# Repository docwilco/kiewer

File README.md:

# kiewer

A site for uploading and sharing KiCad designs, rendered in the browser. The design is in `docs/v1-scope.md` and `docs/adr/`; the vocabulary in `GLOSSARY.md`.

## Development

One-time, after cloning: `git config core.hooksPath .githooks`, then for
the viewer's browser build `rustup target add wasm32-unknown-unknown` and
`cargo install wasm-bindgen-cli --version "$(scripts/wasm-bindgen-version.sh)" --locked`,
and for the sqlx stage
`cargo install sqlx-cli --version "$(scripts/sqlx-version.sh)" --locked --no-default-features --features postgres,rustls`
(each the version Cargo.lock names; CI installs the same way). The hook runs
`scripts/checks.sh` (the stages are listed in its usage line) before every
commit against a snapshot of the index, so unstaged edits never reach the
checks and the working tree stays usable while they run; it needs `rsync`,
`jq` and `cargo-sweep`. CI runs the same script. Run a single stage with
`scripts/checks.sh clippy`. The same setting enables a post-merge hook:
after a merge or pull, fast-forwards included, it removes what the
checkout's target has not used in three days (`.githooks/sweep.sh`, which
the pre-commit hook runs too), and prints a line when it skips.

Running the server: `docker compose up -d` starts Postgres (`compose.yaml`),
`cp .env.example .env` and export it (`set -a; . ./.env; set +a`),
`scripts/build-viewer.sh` once (and again after a change to `kiewer_viewer`
or `kicad_core`: it writes the browser viewer to `kiewer_viewer/dist`, which
`cargo run` embeds; without it the server runs and the viewer page says the
viewer is not built in), then `cargo run`. The first line on stdout is the
build line; the page is at http://localhost:8090/, the viewer with the
hand-off board at http://localhost:8090/viewer, its schematic at
http://localhost:8090/schematic, the upload form at
http://localhost:8090/upload once signed in, and `/health` says `ok` once
the database answers.
`kiewer_lib::config` is the list of variables the server reads and their
defaults; the blob store writes under `blobs/` (git-ignored) unless
`BLOB_BUCKET` names a GCS bucket, which makes it the GCS store (with
`KIEWER_GCS_EMULATOR` beside it, on the emulator below). `FASTLY_SERVICE_ID`
and `FASTLY_API_TOKEN` stay unset here: nothing is in front of the server,
so a write purges nothing. `SURROGATE_KEY_PREFIX` goes in front of every
cache key the server names and purges; `infra/` sets `staging-` on
kiewer-staging, which shares production's Fastly service, and a dev box
leaves it unset. The log is text
on a terminal and JSON lines anywhere else (Cloud Run reads those into
`jsonPayload`; the renderer beacon's metric in `infra/logging.tf` counts
them); `LOG_FORMAT=json` or `text` overrides. Ctrl-c or SIGTERM stops it
after the requests in flight.

The tests that need Postgres (every user of `kiewer_test_support::db`)
run when `DATABASE_URL` is exported; CI sets it against a service
container that matches `compose.yaml`. Without it such a test returns
early and counts as passed, so `scripts/checks.sh test` fails without
it, unless `KIEWER_SKIP_DB_TESTS=1` is set: then they skip, and a loud
line names them before the stages and again after the last. CI refuses
the opt-out. The hook reads the variable from the shell that runs
`git commit`, never from `.env`: each worktree needs a database of its
own, since on a shared one sqlx refuses a worktree that lacks a
migration another applied (`VersionMissing`). Some test modules create
and use a database of their own beside it, the URL's name plus a suffix
(`kiewer_test_support::db::pool_of_its_own`: `_collector`, `_plans`), so
the role needs CREATEDB (compose's and CI's `kiewer` is the image's
superuser). The schema is `migrations/` (its README has the
naming rule).

Every statement in `kiewer_lib` is a `sqlx::query!`, `query_as!` or
`query_scalar!` macro, checked at compile time against the offline data
committed in `.sqlx/`; statement text several statements share is spliced
in by `kiewer_lib/src/sql.rs`. `scripts/checks.sh` and
`scripts/release-build.sh` export `SQLX_OFFLINE=true`, so a build reads
that data and never a database; `.env.example` sets it too, since the
macros read a `.env` here or in any directory above. After a change to a
statement or a migration, `scripts/sqlx-prepare.sh` rewrites `.sqlx/`
against a scratch database beside `DATABASE_URL`'s (its name plus
`_sqlx`, migrated from `migrations/`), and `git add -A .sqlx` stages the
new and the deleted files with the change. The sqlx stage runs it with
`--check` and fails while the data is stale. While a statement is in
flux, build with `SQLX_OFFLINE=false` and `DATABASE_URL` on that scratch
database, which the last prepare left migrated.

Sign-in needs an OAuth app of your own at each provider you want, one per
environment (docs/v1-scope.md, Q57). The callback URL to register is
`PUBLIC_URL` (default `http://localhost:8090`, localhost on `PORT`) plus
`/auth/<provider>/callback`; the client id and secret go in `.env` as
`OAUTH_<PROVIDER>_CLIENT_ID` and `OAUTH_<PROVIDER>_CLIENT_SECRET`, the
names `infra/` hands Cloud Run too. A provider with neither variable is
left off the front page and its `/auth/<provider>` answers 404; one
variable without the other fails startup naming the missing one.

- GitHub: https://github.com/settings/developers, New OAuth App, any name,
  homepage `http://localhost:8090`, callback
  `http://localhost:8090/auth/github/callback`; generate a client secret.
  Variables `OAUTH_GITHUB_*`.
- Discord: https://discord.com/developers/applications, New Application,
  OAuth2, add the redirect `http://localhost:8090/auth/discord/callback`;
  the client id and secret are on that page. The server asks the
  `identify` scope only. Variables `OAUTH_DISCORD_*`.
- Google: https://console.cloud.google.com/apis/credentials, Create
  credentials, OAuth client ID, Web application, authorised redirect URI
  `http://localhost:8090/auth/google/callback`; the consent screen needs
  the `profile` scope only and, while it is in testing, your account as
  a test user. Variables `OAUTH_GOOGLE_*`.

Cookies are `Secure` under an `https` `PUBLIC_URL`, so a dev box over
`http` works in every browser. The sign-in tests use a fake of each
provider on loopback and need no app. Production and staging get their
registrations through Secret Manager, not `.env`.

The GCS store test (`kiewer_lib/tests/it/gcs_blob_store.rs`) runs when
`KIEWER_GCS_EMULATOR` names a
[fake-gcs-server](https://github.com/fsouza/fake-gcs-server), under the
same rule as Postgres: without it `scripts/checks.sh test` fails, unless
`KIEWER_SKIP_GCS_TESTS=1` is set, which CI refuses. On a dev box: the
release binary for your platform (v1.56.1, the version CI pins), then
`fake-gcs-server -scheme http -host 127.0.0.1 -port 8092 -backend memory -public-host 127.0.0.1`
and `export KIEWER_GCS_EMULATOR=http://127.0.0.1:8092`.

The golden-image test (`kiewer_viewer/tests/golden.rs`) renders the
hand-off board headless through wgpu on Vulkan and compares each view
with `viewer-drop/exports/png`; its tolerance is in its module doc. It
needs a Vulkan driver: on a box without a GPU that is Mesa's lavapipe,
`apt install mesa-vulkan-drivers`, the package CI and the Dockerfile
install. Without one it skips with a line saying so; on CI it fails
instead. `cargo run --bin kiewer_render_dev -- viewer-drop/board/midi8knob.kicad_pcb <dir>`
writes the same PNGs for a look.

The browser stage (`scripts/checks.sh browser`, in `all`) loads the board
page in Chrome for Testing's `chrome-headless-shell`, which draws WebGL2 on
SwiftShader with no GPU (`kiewer_lib/tests/it/browser.rs`). On a dev box:
`sudo apt install $(scripts/browser.sh packages)` for the libraries it
links against (Ubuntu 24.04 names), then `scripts/browser.sh install`,
which downloads the version the script pins, checks its SHA-256 and
unpacks it under `~/.cache/kiewer` (it needs `curl` and `unzip`); CI
installs the same way. Without it the stage skips with a line saying so;
on CI it fails instead. The Dockerfile installs neither, though programs
the tests run otherwise go into all three places: the image is
runtime-only and runs no tests.

Clippy is pedantic with no blanket allows: every finding is fixed or carries a
site-level `#[expect(..., reason = "...")]` naming the invariant that makes it safe.

### Exit codes

The executable's non-zero exits, each a kind of `kiewer_lib::error::Error`
(`Exit` there renders this table; a test keeps the two equal). 0 is success;
1, 2, 101 and 126 up are never assigned.

| Code | Kind | Meaning |
|---|---|---|
| 3 | Io | I/O, including the blob store's files |
| 4 | Blob | a blob that is corrupt or a hash that does not parse |
| 5 | Config | the environment is missing or malformed |
| 6 | Db | Postgres, including migrations |
| 7 | Template | a page did not render |
| 8 | Failed | a failure with no better kind |
| 9 | Upstream | a sign-in provider or another service over HTTP |

`kiewer_render_dev`'s, each a kind of `kiewer_viewer::error::Error` (`Exit`
there, the same way); 2 is a usage error.

| Code | Kind | Meaning |
|---|---|---|
| 3 | Io | reading the board or writing a PNG |
| 4 | Board | the board does not parse or has nothing to draw |
| 5 | Gpu | no Vulkan adapter, no device, or a frame that would not read back |
| 6 | Png | a PNG that would not encode or decode |

## Infrastructure

GCP and Fastly are Terraform in `infra/`, applied by hand from a workstation;
CI only deploys Cloud Run revisions with the identity it defines there.
`infra/README.md` is the procedure: bootstrapping the state bucket, the apply,
setting the three repository variables from the outputs, and what a plan after
a CI deploy should show.

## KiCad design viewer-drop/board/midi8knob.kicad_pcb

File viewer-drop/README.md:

# midi8knob board viewer: hand-off

Goal: a website, in the spirit of KiCanvas, that shows this KiCad board as
the eight views below plus the schematic, with pan and zoom, layer toggles,
and labels that become readable as you zoom in. Everything in this folder is
the current static pipeline that produces those views; the site replaces the
static output, not the conventions.

Owner: DocWilco. Board: 8 rotary encoders with WS2812B LEDs, STM32G431KBT6,
USB-C, 4 copper layers.

## What is here

| Path | What |
|---|---|
| `board/midi8knob.kicad_pcb` | The board, KiCad 10 format, with the "Rescue" items already stripped (see gotchas). |
| `board/midi8knob.kicad_sch`, `board/midi8knob.kicad_pro` | Schematic and project. |
| `tools/` | The pipeline. `make-svgs.sh` runs everything; read it first. |
| `exports/midi8knob-<layer>.svg` | One kicad-cli export per layer, board-area page, no drawing sheet. |
| `exports/labels-<layer>.svg`, `labels-<layer>-mirror.svg` | Visible pad, via and track labels per copper layer, from `tools/net_labels.py`. |
| `exports/holes.svg` | Drill holes with copper rims on plated ones, from `tools/holes.py`. |
| `exports/views/NN-*.svg`, `exports/midi8knob-layers.svg` | The eight composed views and the tiled overview, from `tools/compose_svg.py`. |
| `exports/png/` | PNG of every view, the overview, and the schematic. The reference rendering: match these. |
| `exports/midi8knob-schematic.svg` | `kicad-cli sch export svg`, one sheet, A4 landscape. |

## The eight views

Layers stack bottom to top. "board" is the brown FR4 fill from the Edge.Cuts
outline; "bare" is outline only. "labels" are the per-layer label files,
drawn last. "holes" is `holes.svg`.

| # | Header | Stack |
|---|---|---|
| 1 | F.Cu + F.Paste | bare, F.Cu `#C83434`, F.Paste silver, labels F |
| 2 | In1.Cu | bare, In1.Cu `#7FC87F`, labels In1 |
| 3 | In2.Cu | bare, In2.Cu `#CE7D2C`, labels In2 |
| 4 | B.Cu | bare, B.Cu `#4D7FC4`, labels B |
| 5 | F.Cu + F.Paste + F.Mask + F.SilkS | board, F.Cu copper, mask overlay with F.Mask openings, F.Paste, F.SilkS, holes, labels F |
| 6 | B.Cu + B.Paste + B.Mask + B.SilkS, mirrored | as 5 with B layers, whole panel flipped left-right, labels from the `-mirror` file drawn unflipped |
| 7 | F.Cu + B.Cu + F.SilkS + B.SilkS + F.CrtYd + B.CrtYd | bare, B.Cu `#4D7FC4`, F.Cu `#C83434` at opacity 0.8, B.SilkS, F.SilkS, B.CrtYd `#26E9FF`, F.CrtYd `#FF26E2`, holes, labels B then F |
| 8 | B.Cu + F.Cu + ... | as 7 with F.Cu underneath and B.Cu on top at 0.8, labels F then B |

Colours (`tools/compose_svg.py`, duplicated in `tools/holes.py`): page
`#2b2b2b`, board `#7a5a32`, copper `#f0c030`, paste `#c9c9c9`, mask
`#1f8a3f` at opacity 0.7, outline `#D0D2CD`. Views 1 to 4 and 7, 8 use the
KiCad default theme colours instead of copper yellow.

## How a view is composed

- **Coordinates.** Every export shares one viewBox, `0 0 111.9886 57.9882`
  mm, origin at the Edge.Cuts bounding box (kicad-cli `--page-size-mode 2`).
  Board coordinates map to it by subtracting the Edge.Cuts minimum, which
  `tools/kicad_board.py` computes. Labels and holes are generated straight
  from the board file in that frame.
- **Board fill.** The Edge.Cuts export is stroked segments and arcs;
  `outline_path()` chains them into one closed path.
- **Mask overlay.** The mask layer in KiCad is the openings. The overlay is
  the board path in mask colour with an SVG luminance `<mask>` that is white
  everywhere and black where the F.Mask/B.Mask export has shapes.
- **Holes.** kicad-cli draws drill marks white on copper layers and black on
  every other layer; the composer recolours both to the page background.
  `holes.svg` redraws them with a copper rim for plated holes, from pad
  type (`thru_hole` plated, `np_thru_hole` bare) and via drill.
- **Labels.** Pad number and net inside the pad, net on vias and along
  track segments. Font size fits the item (monospace, 0.6 em per glyph),
  labels under 0.08 mm are dropped. Angle follows the pad or track long
  axis, normalised to (-90, 90]; round and square pads stay upright.
- **Mirror.** `<g transform="translate(w 0) scale(-1 1)">` around the
  layers; label files for mirrored views have x flipped and angles negated
  so the text reads normally.
- **Zoom.** The composed SVGs declare width and height 10x the viewBox
  because browsers cap zoom relative to the natural size. A site with its
  own pan/zoom drops that.

## kicad-cli SVG conventions worth knowing

- Shapes carry colour in `style="fill:#RRGGBB; ..."` strings, theme colours
  per layer. Recolouring is a string replace on those.
- Oval pads and oval mask openings are round-capped stroked `<path>` lines,
  not filled shapes. Anything that treats "fill" as the only colour misses
  them.
- Text on the silkscreen is already paths; the exports need no font. The
  label files use `font-family="Consolas, monospace"` as live `<text>`.
- `--subtract-soldermask` was on for the silkscreen export.

## Gotchas

- **Rescue layer.** The JLCPCB-converted footprints (J1 USB-C, SW5, SW10)
  carry body art on an undefined "Rescue" layer. The KiCad GUI tolerates it;
  kicad-cli refuses the board. `tools/strip_rescue.py` writes a cleaned copy,
  and `board/midi8knob.kicad_pcb` here is that copy.
- **Fonts.** Silkscreen uses Consolas with knockout. Regenerating the
  exports with kicad-cli needs the font installed (`~/.fonts/consola.ttf`,
  `fc-cache -f`); otherwise it substitutes DejaVu Sans Mono and the labels
  shift. Not in this folder; proprietary.
- **File names.** `kicad-cli sch export svg` names its output after the
  project, `midi8knob.svg`, which collides with the `midi8knob.svg/` output
  directory in the repo. The pipeline exports to a temp dir and moves it.
- **Line endings.** Board and schematic files are CRLF. Nets are written as
  `(net "name")` without numbers in this format version.
- **Dependencies** to rerun the pipeline: kicad-cli 10.0.8 (Ubuntu PPA
  `ppa:kicad/kicad-10.0-releases`), `rsvg-convert` from `librsvg2-bin`,
  Python 3, the font above.

## Open

- Site stack is undecided. KiCanvas itself parses `.kicad_pcb` and renders
  in WebGL; this pipeline instead pre-renders with kicad-cli. Either route
  must reproduce the eight stacks and the label and hole rules above.
- Whether the site reads the board file at runtime or ships the exports.
- Hover or click on a net to highlight it is wanted but not built; the
  label files and `tools/kicad_board.py` give net names per item.

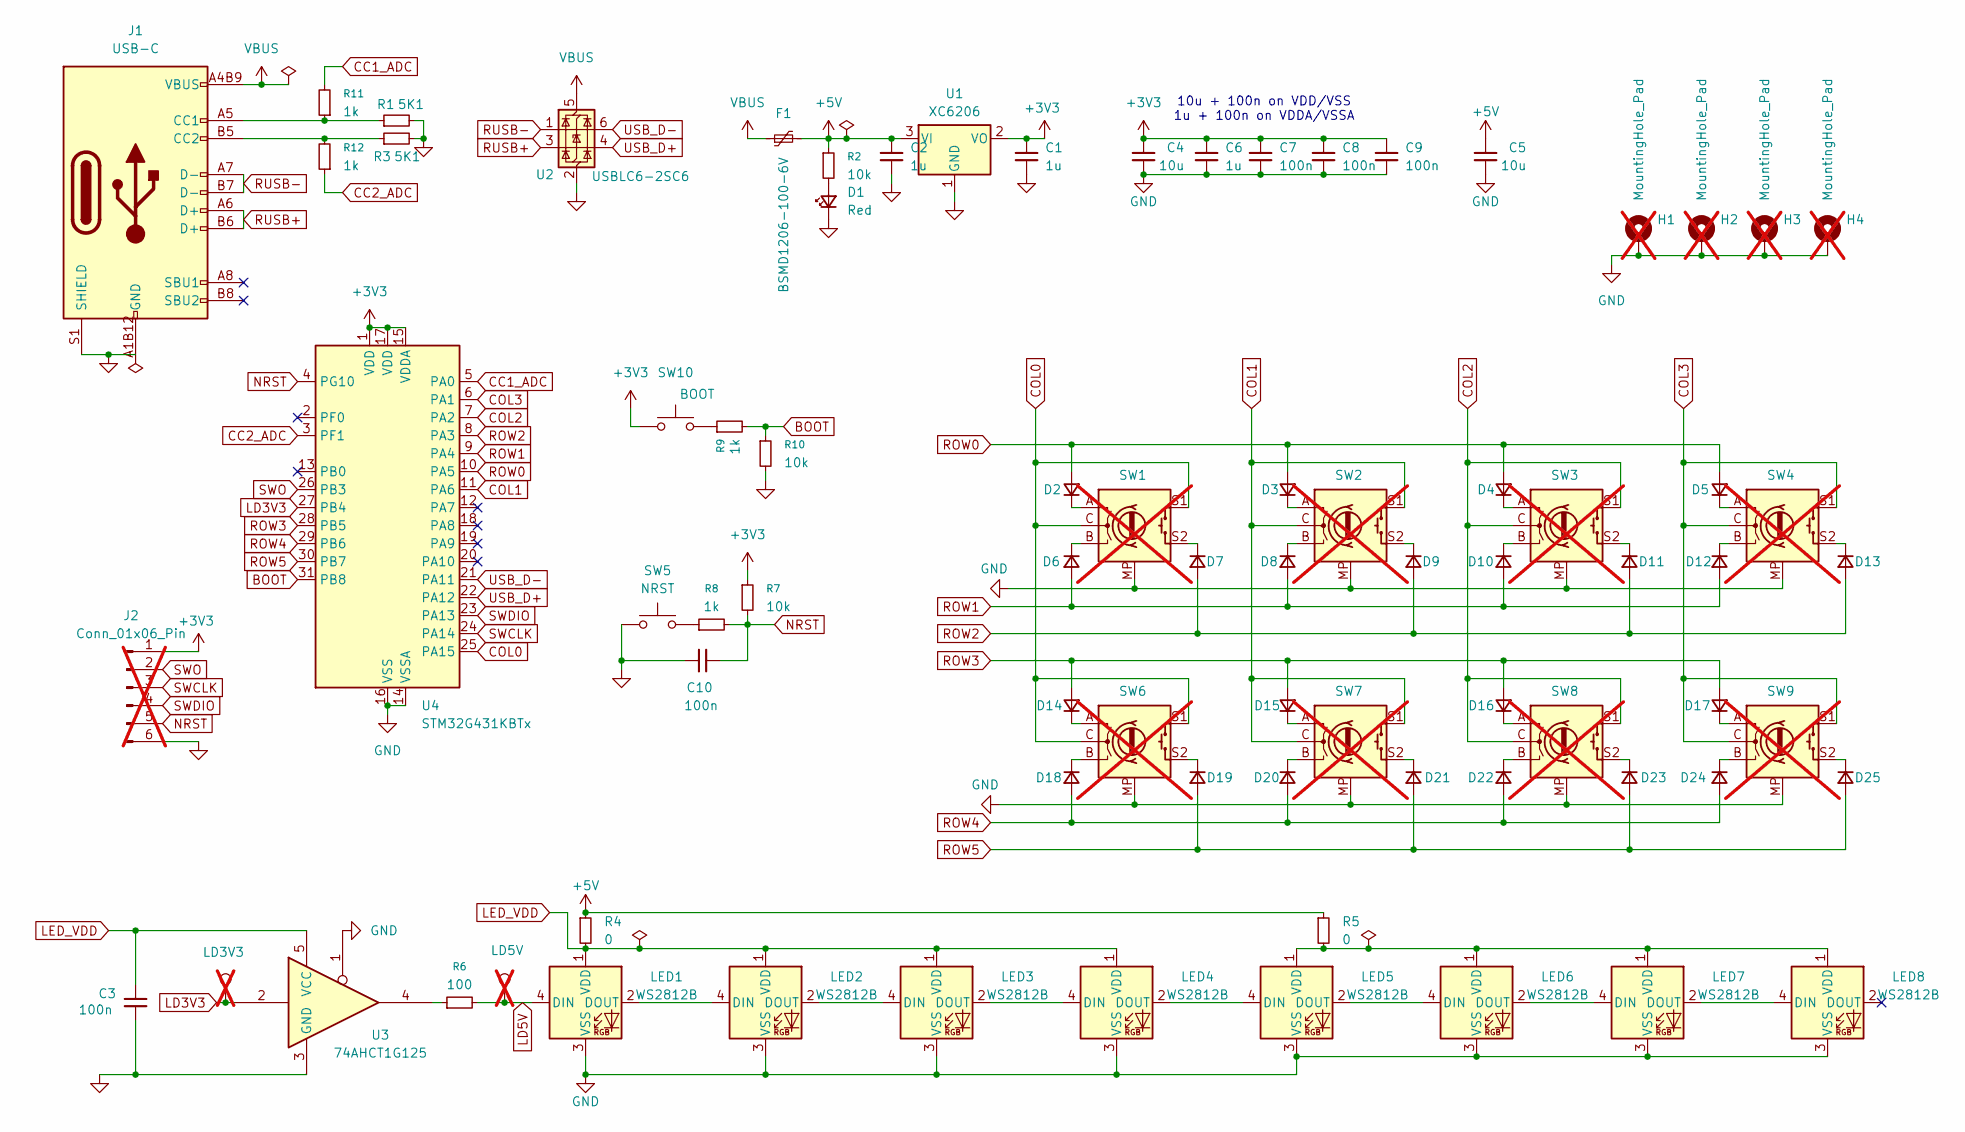
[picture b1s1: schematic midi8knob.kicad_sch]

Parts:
C1, C2, C6: 1u; C_0402_1005Metric; LCSC C52923
C3, C7, C8, C9, C10: 100n; C_0402_1005Metric; LCSC C1525
C4, C5: 10u; C_0603_1608Metric; LCSC C19702
D1: Red; LED_0603_1608Metric; LCSC C2286
D2, D3, D4, D5, D6, D7, D8, D9, D10, D11, D12, D13, D14, D15, D16, D17, D18, D19, D20, D21, D22, D23, D24, D25: D_Small; D_SOD-323; LCSC C437156
F1: BSMD1206-100-6V; Fuse_1206_3216Metric; LCSC C883129
H1, H2, H3, H4: MountingHole_Pad; MountingHole_3.2mm_M3_Pad_Via; not fitted
J1: USB-C; USB-C_SMD-TYPE-C-31-M-12_1; LCSC C165948
J2: Conn_01x06_Pin; PinHeader_1x06_P2.54mm_Vertical; not fitted
LED1, LED2, LED3, LED4, LED5, LED6, LED7, LED8: WS2812B; LED_WS2812B_PLCC4_5.0x5.0mm_P3.2mm; LCSC C52941391
R1, R3: 5K1; R_0402_1005Metric; LCSC C25905
R2, R7, R10: 10k; R_0402_1005Metric; LCSC C25744
R4, R5: 0; R_0402_1005Metric; LCSC C17168
R6: 100; R_0402_1005Metric; LCSC C25076
R8, R9, R11, R12: 1k; R_0402_1005Metric; LCSC C11702
SW1, SW2, SW3, SW4, SW6, SW7, SW8, SW9: RotaryEncoder_Switch_MP; XDCR_PEC11R-4020F-S0024; not fitted
SW5: NRST; SW-SMD_L3.9-W3.0-P4.45; LCSC C720477
SW10: BOOT; SW-SMD_L3.9-W3.0-P4.45; LCSC C720477
TP1: LD3V3; TestPoint_Pad_D1.0mm; not fitted
TP2: LD5V; TestPoint_Pad_D1.0mm; not fitted
U1: XC6206; SOT-23-3; LCSC C5446
U2: USBLC6-2SC6; SOT-23-6; LCSC C7519
U3: 74AHCT1G125; SOT-353_SC-70-5; LCSC C7039245
U4: STM32G431KBTx; LQFP-32_7x7mm_P0.8mm; LCSC C5270317

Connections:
+3V3: C1.1, C4.1, C6.1, C7.1, C8.1, C9.1, J2.1, R7.1, SW10.1, U1.2 (VO), U4.1 (VDD), U4.15 (VDDA), U4.17 (VDD)
+5V: C2.1, C5.1, F1.2, R2.1, R4.1, R5.1, U1.3 (VI)
BOOT: R9.2, R10.1, U4.31 (PB8)
CC1_ADC: R11.2, U4.5 (PA0)
CC2_ADC: R12.1, U4.3 (PF1)
COL0: SW1.C, SW1.S1, SW6.C, SW6.S1, U4.25 (PA15)
COL1: SW2.C, SW2.S1, SW7.C, SW7.S1, U4.11 (PA6)
COL2: SW3.C, SW3.S1, SW8.C, SW8.S1, U4.7 (PA2)
COL3: SW4.C, SW4.S1, SW9.C, SW9.S1, U4.6 (PA1)
GND: C1.2, C2.2, C3.2, C4.2, C5.2, C6.2, C7.2, C8.2, C9.2, C10.1, D1.1 (K), H1.1 (1_1), H2.1 (1_1), H3.1 (1_1), H4.1 (1_1), J1.A1B12 (GND), J1.B1A12 (GND), J1.S1 (SHIELD), J2.6, LED1.3 (VSS), LED2.3 (VSS), LED3.3 (VSS), LED4.3 (VSS), LED5.3 (VSS), LED6.3 (VSS), LED7.3 (VSS), LED8.3 (VSS), R1.2, R3.2, R10.2, SW1.MP, SW2.MP, SW3.MP, SW4.MP, SW5.1, SW6.MP, SW7.MP, SW8.MP, SW9.MP, U1.1 (GND), U2.2 (GND), U3.1, U3.3 (GND), U4.14 (VSSA), U4.16 (VSS), U4.32 (VSS)
LD3V3: TP1.1 (1_1), U3.2, U4.27 (PB4)
LD5V: LED1.4 (DIN), R6.2, TP2.1 (1_1)
LED_VDD: C3.1, LED1.1 (VDD), LED2.1 (VDD), LED3.1 (VDD), LED4.1 (VDD), R4.2, U3.5 (VCC)
NRST: C10.2, J2.5, R7.2, R8.2, U4.4 (PG10)
unnamed: D1.2 (A), R2.2
unnamed: D2.1 (K), SW1.A
unnamed: D3.1 (K), SW2.A
unnamed: D4.1 (K), SW3.A
unnamed: D5.1 (K), SW4.A
unnamed: D6.1 (K), SW1.B
unnamed: D7.1 (K), SW1.S2
unnamed: D8.1 (K), SW2.B
unnamed: D9.1 (K), SW2.S2
unnamed: D10.1 (K), SW3.B
unnamed: D11.1 (K), SW3.S2
unnamed: D12.1 (K), SW4.B
unnamed: D13.1 (K), SW4.S2
unnamed: D14.1 (K), SW6.A
unnamed: D15.1 (K), SW7.A
unnamed: D16.1 (K), SW8.A
unnamed: D17.1 (K), SW9.A
unnamed: D18.1 (K), SW6.B
unnamed: D19.1 (K), SW6.S2
unnamed: D20.1 (K), SW7.B
unnamed: D21.1 (K), SW7.S2
unnamed: D22.1 (K), SW8.B
unnamed: D23.1 (K), SW8.S2
unnamed: D24.1 (K), SW9.B
unnamed: D25.1 (K), SW9.S2
unnamed: J1.A5 (CC1), R1.1, R11.1
unnamed: J1.B5 (CC2), R3.1, R12.2
unnamed: LED1.2 (DOUT), LED2.4 (DIN)
unnamed: LED2.2 (DOUT), LED3.4 (DIN)
unnamed: LED3.2 (DOUT), LED4.4 (DIN)
unnamed: LED4.2 (DOUT), LED5.4 (DIN)
unnamed: LED5.2 (DOUT), LED6.4 (DIN)
unnamed: LED5.1 (VDD), LED6.1 (VDD), LED7.1 (VDD), LED8.1 (VDD), R5.2
unnamed: LED6.2 (DOUT), LED7.4 (DIN)
unnamed: LED7.2 (DOUT), LED8.4 (DIN)
unnamed: R6.1, U3.4
unnamed: R8.1, SW5.2
unnamed: R9.1, SW10.2
ROW0: D2.2 (A), D3.2 (A), D4.2 (A), D5.2 (A), U4.10 (PA5)
ROW1: D6.2 (A), D8.2 (A), D10.2 (A), D12.2 (A), U4.9 (PA4)
ROW2: D7.2 (A), D9.2 (A), D11.2 (A), D13.2 (A), U4.8 (PA3)
ROW3: D14.2 (A), D15.2 (A), D16.2 (A), D17.2 (A), U4.28 (PB5)
ROW4: D18.2 (A), D20.2 (A), D22.2 (A), D24.2 (A), U4.29 (PB6)
ROW5: D19.2 (A), D21.2 (A), D23.2 (A), D25.2 (A), U4.30 (PB7)
RUSB+: J1.A6 (D+), J1.B6 (D+), U2.3 (I/O2)
RUSB-: J1.A7 (D-), J1.B7 (D-), U2.1 (I/O1)
SWCLK: J2.3, U4.24 (PA14)
SWDIO: J2.4, U4.23 (PA13)
SWO: J2.2, U4.26 (PB3)
USB_D+: U2.4 (I/O2), U4.22 (PA12)
USB_D-: U2.6 (I/O1), U4.21 (PA11)
VBUS: F1.1, J1.A4B9 (VBUS), J1.B4A9 (VBUS), U2.5 (VBUS)

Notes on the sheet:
10u + 100n on VDD/VSS 1u + 100n on VDDA/VSSA

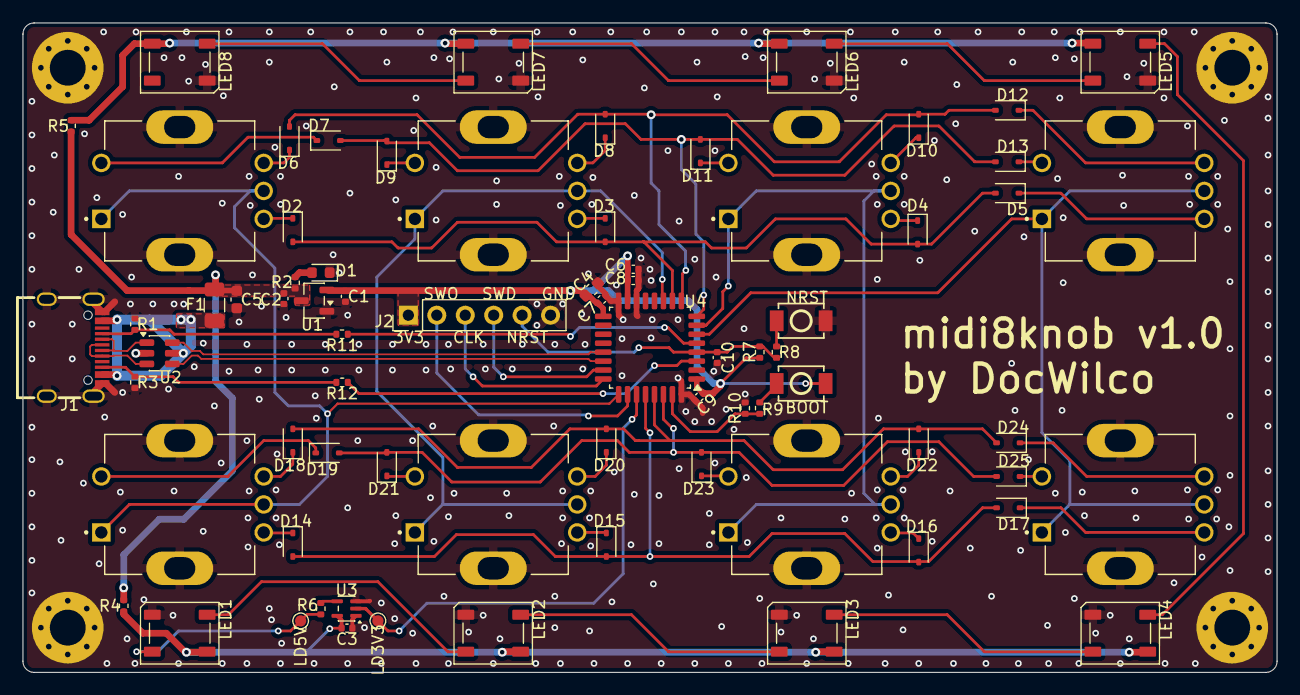
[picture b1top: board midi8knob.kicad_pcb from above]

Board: 4 copper layers, 112.0 x 58.0 mm, 78 parts (0 on the bottom side), 66 nets.
